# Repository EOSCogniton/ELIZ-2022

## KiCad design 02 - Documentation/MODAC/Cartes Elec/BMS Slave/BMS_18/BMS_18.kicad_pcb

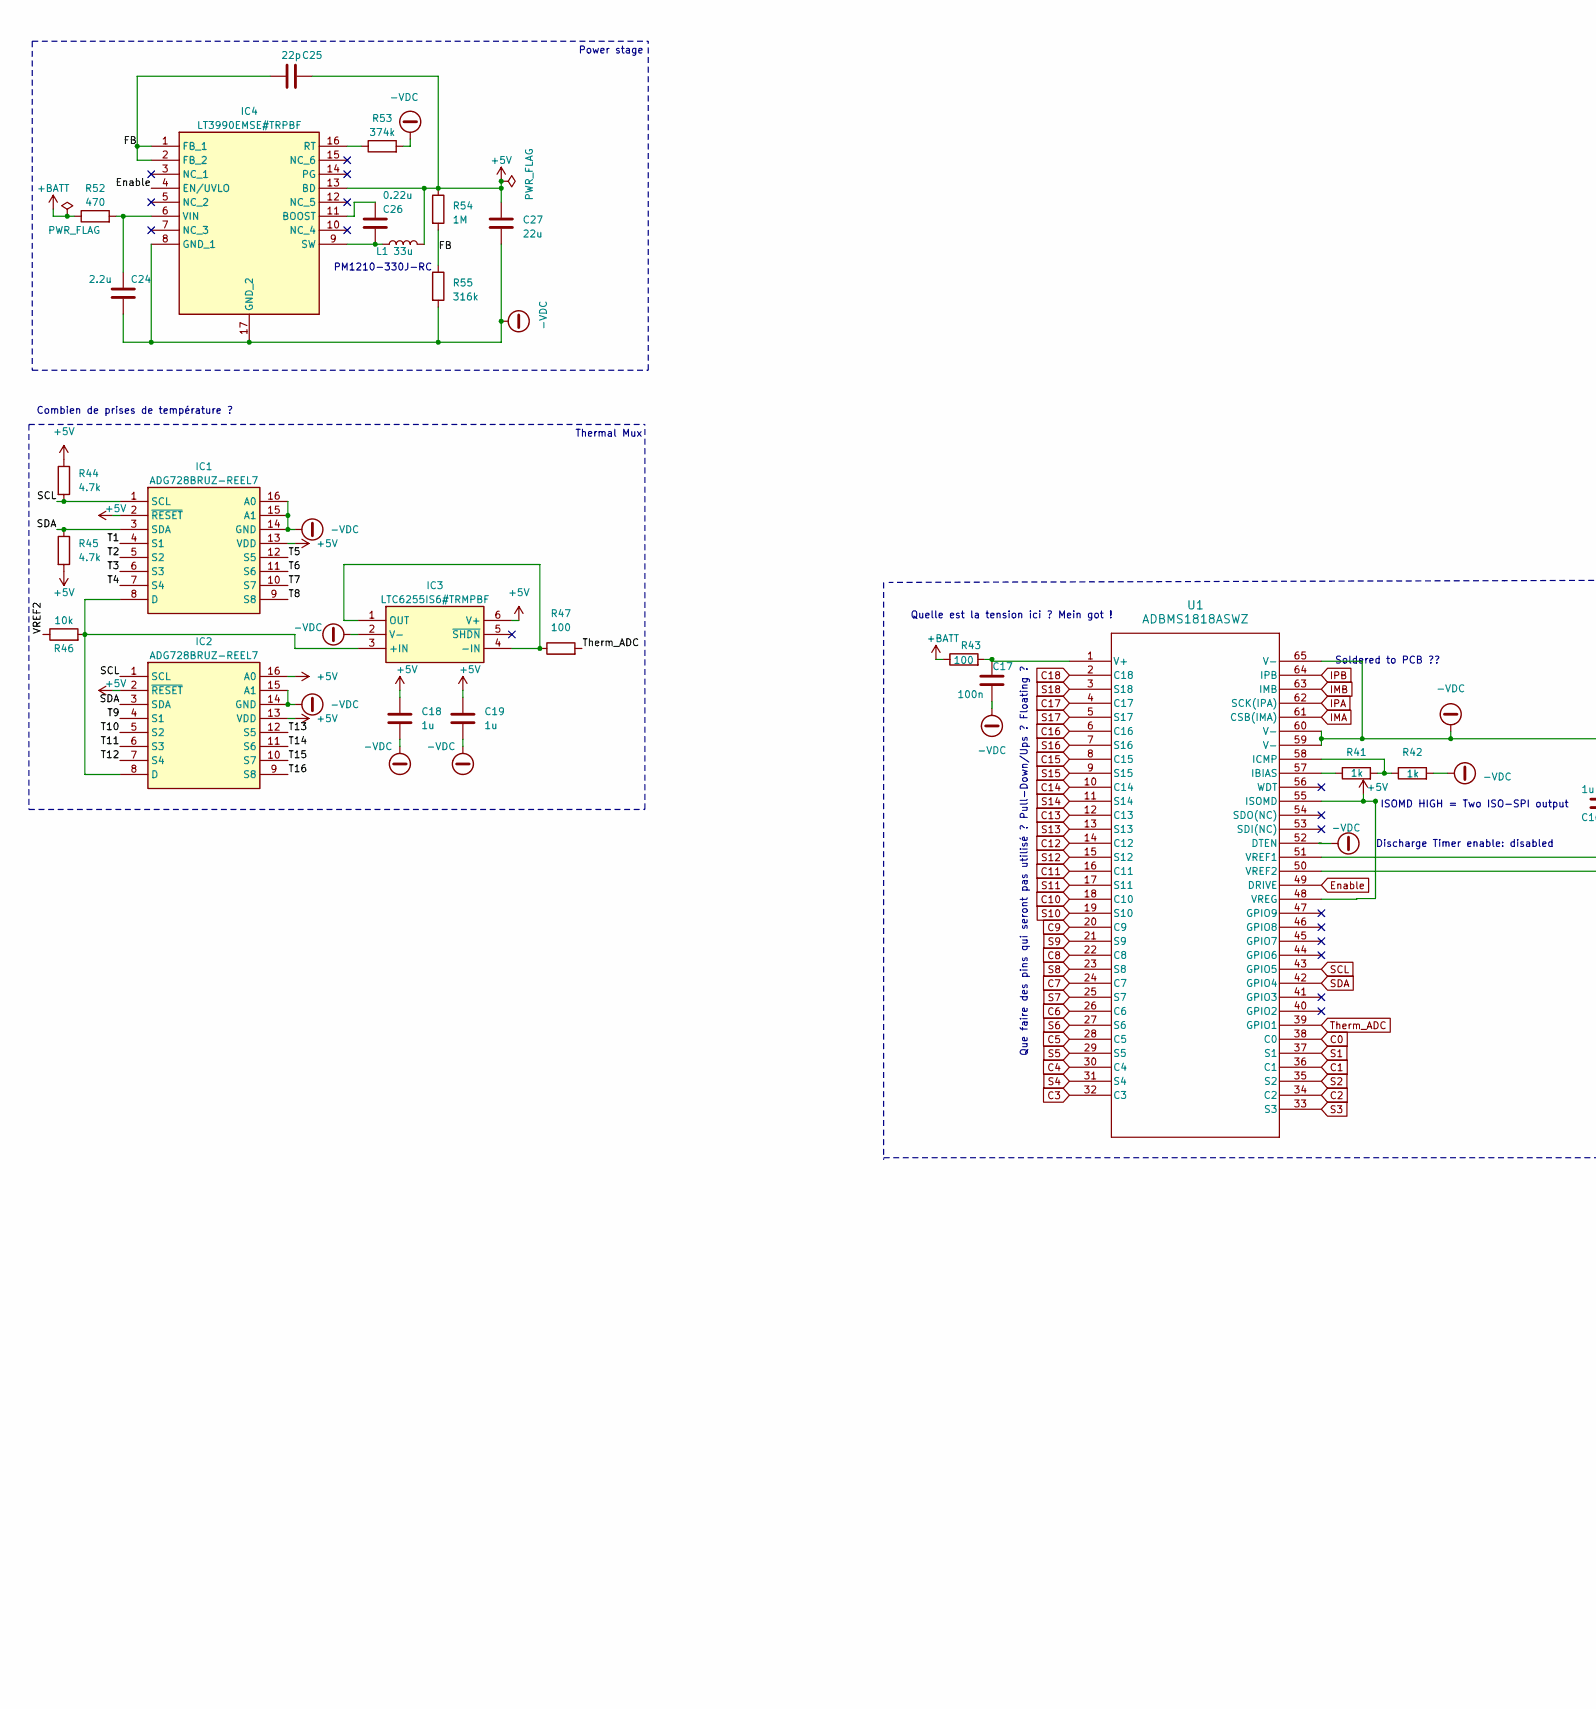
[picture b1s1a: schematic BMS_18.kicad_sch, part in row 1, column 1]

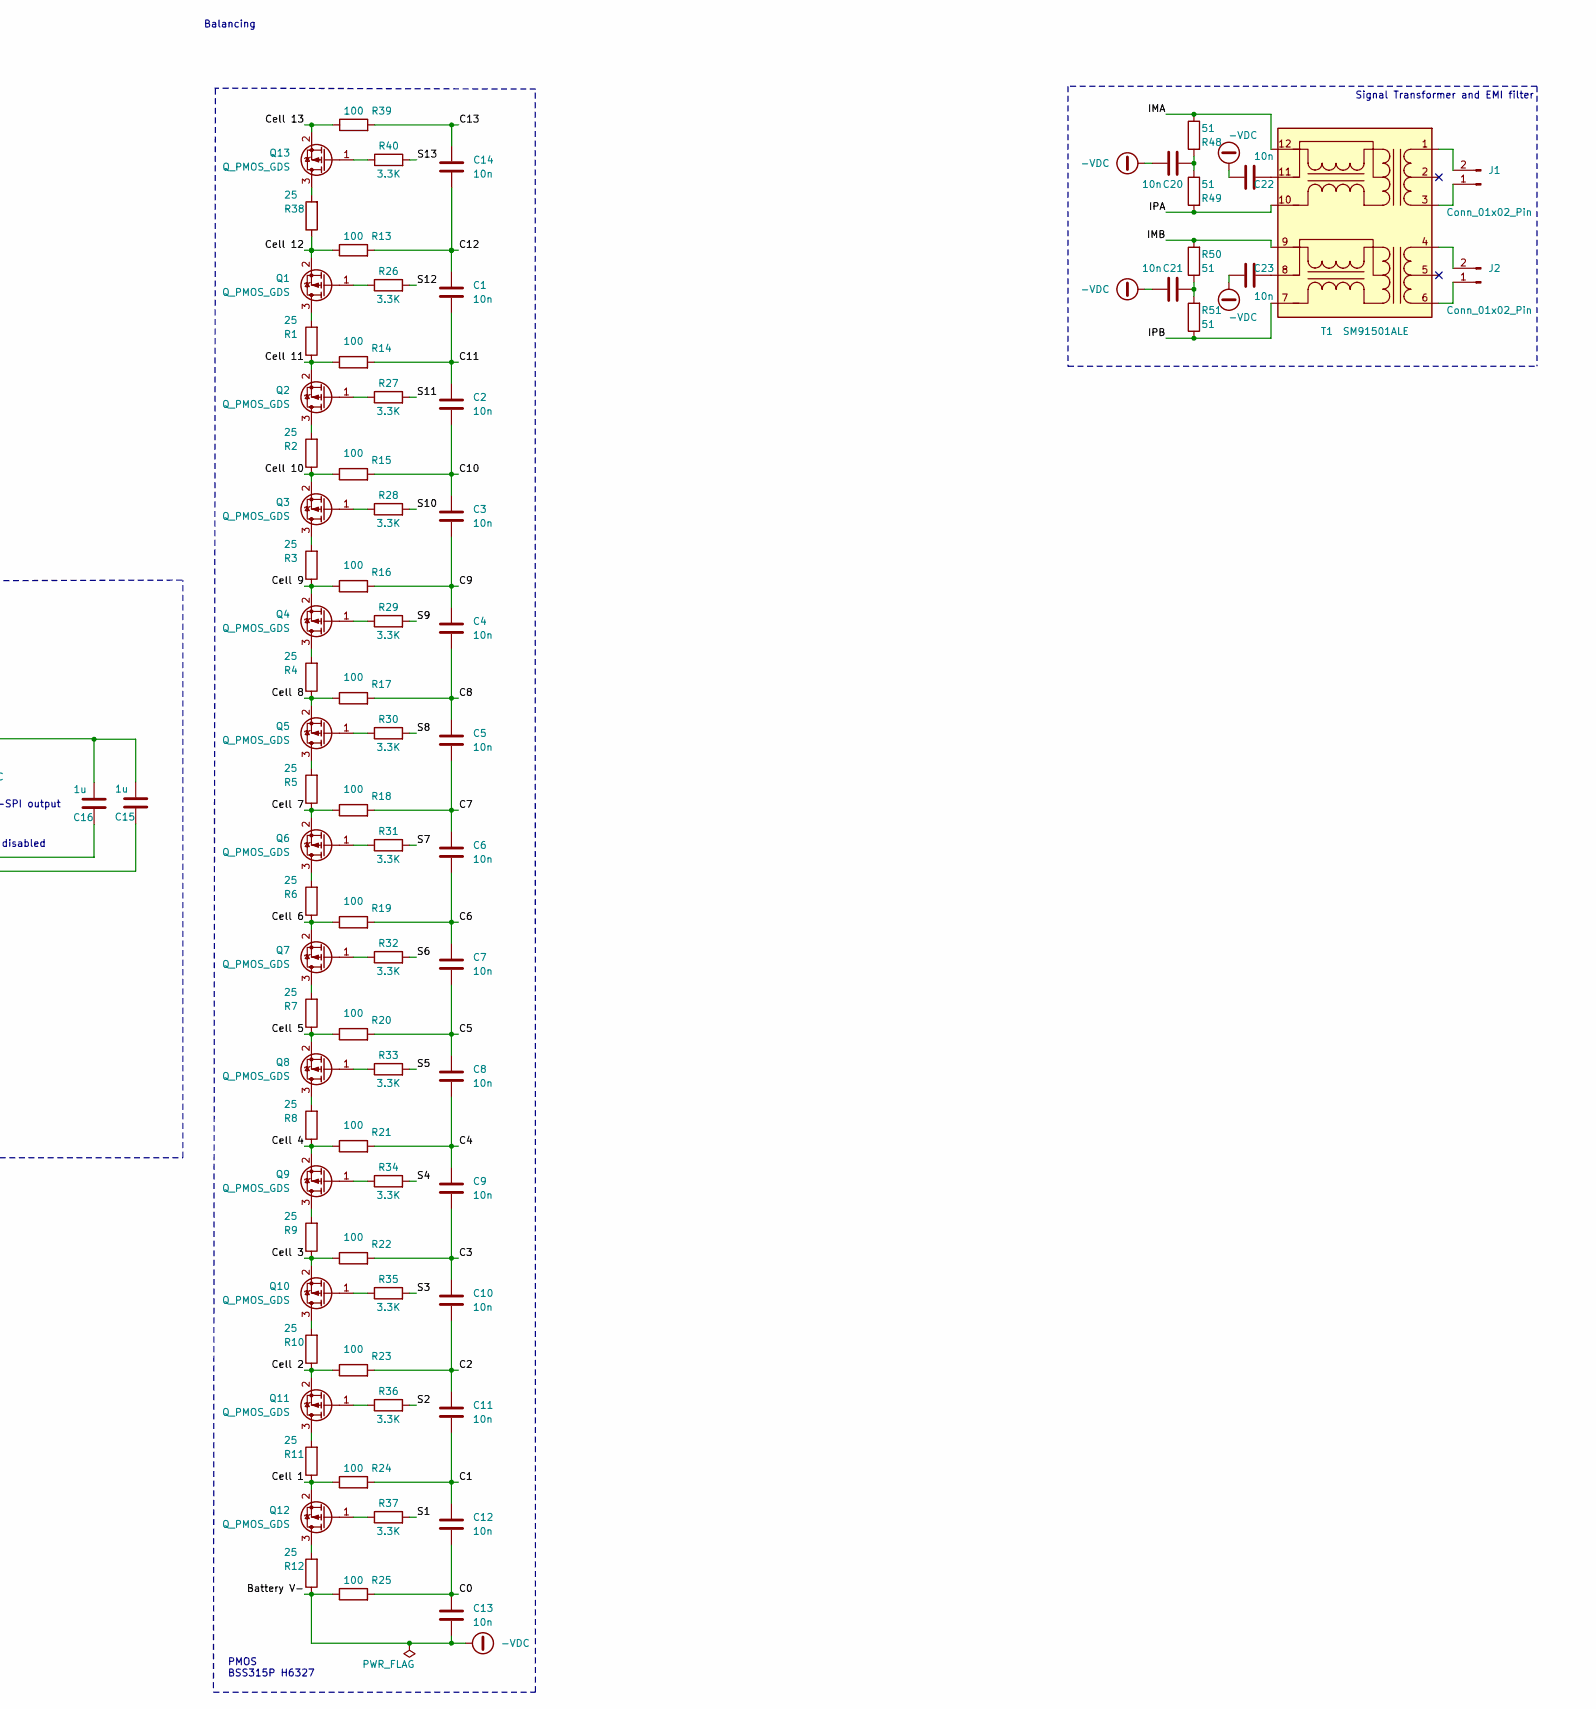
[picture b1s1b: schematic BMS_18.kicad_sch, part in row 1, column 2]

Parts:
C1, C2, C3, C4, C5, C6, C7, C8, C9, C10, C11, C12, C13, C14, C20, C21, C22, C23: 10n; C_0805_2012Metric_Pad1.18x1.45mm_HandSolder
C15, C16, C18, C19: 1u; C_0805_2012Metric_Pad1.18x1.45mm_HandSolder
C17: 100n; C_0805_2012Metric_Pad1.18x1.45mm_HandSolder
C24: 2.2u; C_0805_2012Metric_Pad1.18x1.45mm_HandSolder
C25: 22p; C_0805_2012Metric_Pad1.18x1.45mm_HandSolder
C26: 0.22u; C_0805_2012Metric_Pad1.18x1.45mm_HandSolder
C27: 22u; C_0805_2012Metric_Pad1.18x1.45mm_HandSolder
IC1, IC2: ADG728BRUZ-REEL7; SOP65P640X120-16N; Mouser Part Number 584-ADG728BRUZ-R7
IC3: LTC6255IS6#TRMPBF; SOT95P280X100-6N; Mouser Part Number 584-LTC6255IS6TRMPBF
IC4: LT3990EMSE#TRPBF; SOP50P490X110-17N; Mouser Part Number 584-LT3990EMSE#TRPBF
J1, J2: Conn_01x02_Pin; RHDR2W97P0X254_1X2_654X508X1379P
L1: 33u; L_1210_3225Metric_Pad1.42x2.65mm_HandSolder
Q1, Q2, Q3, Q4, Q5, Q6, Q7, Q8, Q9, Q10, Q11, Q12, Q13: Q_PMOS_GDS; SOT95P237X112-3N
R1, R2, R3, R4, R5, R6, R7, R8, R9, R10, R11, R12, R38: 25; R_2512_6332Metric_Pad1.40x3.35mm_HandSolder
R13, R14, R15, R16, R17, R18, R19, R20, R21, R22, R23, R24, R25, R39, R43, R47: 100; R_1206_3216Metric_Pad1.30x1.75mm_HandSolder
R26, R27, R28, R29, R30, R31, R32, R33, R34, R35, R36, R37, R40: 3.3K; R_1206_3216Metric_Pad1.30x1.75mm_HandSolder
R41, R42: 1k; R_1206_3216Metric_Pad1.30x1.75mm_HandSolder
R44, R45: 4.7k; R_1206_3216Metric_Pad1.30x1.75mm_HandSolder
R46: 10k; R_1206_3216Metric_Pad1.30x1.75mm_HandSolder
R48, R49, R50, R51: 51; R_1206_3216Metric_Pad1.30x1.75mm_HandSolder
R52: 470; R_1206_3216Metric_Pad1.30x1.75mm_HandSolder
R53: 374k; R_1206_3216Metric_Pad1.30x1.75mm_HandSolder
R54: 1M; R_1206_3216Metric_Pad1.30x1.75mm_HandSolder
R55: 316k; R_1206_3216Metric_Pad1.30x1.75mm_HandSolder
T1: SM91501ALE; SOP200P1473X500-12N; Mouser Part Number 652-SM91501ALE
U1: ADBMS1818ASWZ; 05-08-1982_ADI

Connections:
+5V: C18.1, C19.1, C25.2, C27.2, IC1.2 (~RESET), IC1.13 (VDD), IC2.2 (~RESET), IC2.13 (VDD), IC2.16 (A0), IC3.6 (V+), IC4.13 (BD), L1.2, R44.1, R45.2, R54.1, U1.48 (VREG), U1.55 (ISOMD)
+BATT: R43.1, R52.1
-VDC: C13.2, C15.2, C16.2, C17.2, C18.2, C19.2, C20.1, C21.1, C22.1, C23.1, C24.1, C27.1, IC1.14 (GND), IC1.15 (A1), IC1.16 (A0), IC2.14 (GND), IC2.15 (A1), IC3.2 (V-), IC4.8 (GND_1), IC4.17 (GND_2), R12.1, R25.1, R42.2, R53.2, R55.2, U1.52 (DTEN), U1.59 (V-), U1.60 (V-), U1.65 (V-)
/Cell 1: Q12.2 (S), R11.1, R24.1
/Cell 2: Q11.2 (S), R10.1, R23.1
/Cell 3: Q10.2 (S), R9.1, R22.1
/Cell 4: Q9.2 (S), R8.1, R21.1
/Cell 5: Q8.2 (S), R7.1, R20.1
/Cell 6: Q7.2 (S), R6.1, R19.1
/Cell 7: Q6.2 (S), R5.1, R18.1
/Cell 8: Q5.2 (S), R4.1, R17.1
/Cell 9: Q4.2 (S), R3.1, R16.1
/Cell 10: Q3.2 (S), R2.1, R15.1
/Cell 11: Q2.2 (S), R1.1, R14.1
/Cell 12: Q1.2 (S), R13.1, R38.1
/Cell 13: Q13.2 (S), R39.1
/FB: C25.1, IC4.1 (FB_1), IC4.2 (FB_2), R54.2, R55.1
/T1: IC1.4 (S1)
/T2: IC1.5 (S2)
/T3: IC1.6 (S3)
/T4: IC1.7 (S4)
/T5: IC1.12 (S5)
/T6: IC1.11 (S6)
/T7: IC1.10 (S7)
/T8: IC1.9 (S8)
/T9: IC2.4 (S1)
/T10: IC2.5 (S2)
/T11: IC2.6 (S3)
/T12: IC2.7 (S4)
/T13: IC2.12 (S5)
/T14: IC2.11 (S6)
/T15: IC2.10 (S7)
/T16: IC2.9 (S8)
/VREF2: R46.1
C0: C12.2, C13.1, R25.2, U1.38 (C0)
C1: C11.2, C12.1, R24.2, U1.36 (C1)
C2: C10.2, C11.1, R23.2, U1.34 (C2)
C3: C9.2, C10.1, R22.2, U1.32 (C3)
C4: C8.2, C9.1, R21.2, U1.30 (C4)
C5: C7.2, C8.1, R20.2, U1.28 (C5)
C6: C6.2, C7.1, R19.2, U1.26 (C6)
C7: C5.2, C6.1, R18.2, U1.24 (C7)
C8: C4.2, C5.1, R17.2, U1.22 (C8)
C9: C3.2, C4.1, R16.2, U1.20 (C9)
C10: C2.2, C3.1, R15.2, U1.18 (C10)
C11: C1.2, C2.1, R14.2, U1.16 (C11)
C12: C1.1, C14.2, R13.2, U1.14 (C12)
C13: C14.1, R39.2, U1.12 (C13)
C14: U1.10 (C14)
C15: U1.8 (C15)
C16: U1.6 (C16)
C17: U1.4 (C17)
C18: U1.2 (C18)
Enable: IC4.4 (EN/UVLO), U1.49 (DRIVE)
IMA: R48.1, T1.12 (SEC1_3), U1.61 (CSB(IMA))
IMB: R50.2, T1.9 (SEC2_3), U1.63 (IMB)
IPA: R49.2, T1.10 (SEC1_1), U1.62 (SCK(IPA))
IPB: R51.1, T1.7 (SEC2_1), U1.64 (IPB)
unnamed: C20.2, R48.2, R49.1
unnamed: C21.2, R50.1, R51.2
unnamed: IC1.8 (D), IC2.8 (D), IC3.3 (+IN), R46.2
unnamed: IC3.1 (OUT), IC3.4 (-IN), R47.1
unnamed: C26.2, IC4.11 (BOOST)
unnamed: IC4.16 (RT), R53.1
unnamed: C26.1, IC4.9 (SW), L1.1
unnamed: C24.2, IC4.6 (VIN), R52.2
unnamed: J1.1, T1.3 (PRI1_3)
unnamed: J1.2, T1.1 (PRI1_1)
unnamed: J2.1, T1.6 (PRI2_3)
unnamed: J2.2, T1.4 (PRI2_1)
unnamed: Q1.3 (D), R1.2
unnamed: Q1.1 (G), R26.1
unnamed: Q2.3 (D), R2.2
unnamed: Q2.1 (G), R27.1
unnamed: Q3.3 (D), R3.2
unnamed: Q3.1 (G), R28.1
unnamed: Q4.3 (D), R4.2
unnamed: Q4.1 (G), R29.1
unnamed: Q5.3 (D), R5.2
unnamed: Q5.1 (G), R30.1
unnamed: Q6.3 (D), R6.2
unnamed: Q6.1 (G), R31.1
unnamed: Q7.3 (D), R7.2
unnamed: Q7.1 (G), R32.1
unnamed: Q8.3 (D), R8.2
unnamed: Q8.1 (G), R33.1
unnamed: Q9.3 (D), R9.2
unnamed: Q9.1 (G), R34.1
unnamed: Q10.3 (D), R10.2
unnamed: Q10.1 (G), R35.1
unnamed: Q11.3 (D), R11.2
unnamed: Q11.1 (G), R36.1
unnamed: Q12.3 (D), R12.2
unnamed: Q12.1 (G), R37.1
unnamed: Q13.3 (D), R38.2
unnamed: Q13.1 (G), R40.1
unnamed: C22.2, T1.11 (SEC1_2)
unnamed: C23.2, T1.8 (SEC2_2)
unnamed: R41.1, U1.57 (IBIAS)
unnamed: R41.2, R42.1, U1.58 (ICMP)
unnamed: C17.1, R43.2, U1.1 (V+)
unnamed: C16.1, U1.51 (VREF1)
unnamed: C15.1, U1.50 (VREF2)
S1: R37.2, U1.37 (S1)
S2: R36.2, U1.35 (S2)
S3: R35.2, U1.33 (S3)
S4: R34.2, U1.31 (S4)
S5: R33.2, U1.29 (S5)
S6: R32.2, U1.27 (S6)
S7: R31.2, U1.25 (S7)
S8: R30.2, U1.23 (S8)
S9: R29.2, U1.21 (S9)
S10: R28.2, U1.19 (S10)
S11: R27.2, U1.17 (S11)
S12: R26.2, U1.15 (S12)
S13: R40.2, U1.13 (S13)
S14: U1.11 (S14)
S15: U1.9 (S15)
S16: U1.7 (S16)
S17: U1.5 (S17)
S18: U1.3 (S18)
SCL: IC1.1 (SCL), IC2.1 (SCL), R44.2, U1.43 (GPIO5)
SDA: IC1.3 (SDA), IC2.3 (SDA), R45.1, U1.42 (GPIO4)
Therm_ADC: R47.2, U1.39 (GPIO1)

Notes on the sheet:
PM1210-330J-RC
Combien de prises de température ?
Signal Transformer and EMI filter
Discharge Timer enable: disabled
Quelle est la tension ici ? Mein got !
Soldered to PCB ??
Power stage
Balancing
Thermal Mux
ISOMD HIGH = Two ISO-SPI output
Que faire des pins qui seront pas utilisé ? Pull-Down/Ups ? Floating ?
PMOS BSS315P H6327

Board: 2 copper layers, 104 parts (0 on the bottom side), 97 nets, no tracks yet.

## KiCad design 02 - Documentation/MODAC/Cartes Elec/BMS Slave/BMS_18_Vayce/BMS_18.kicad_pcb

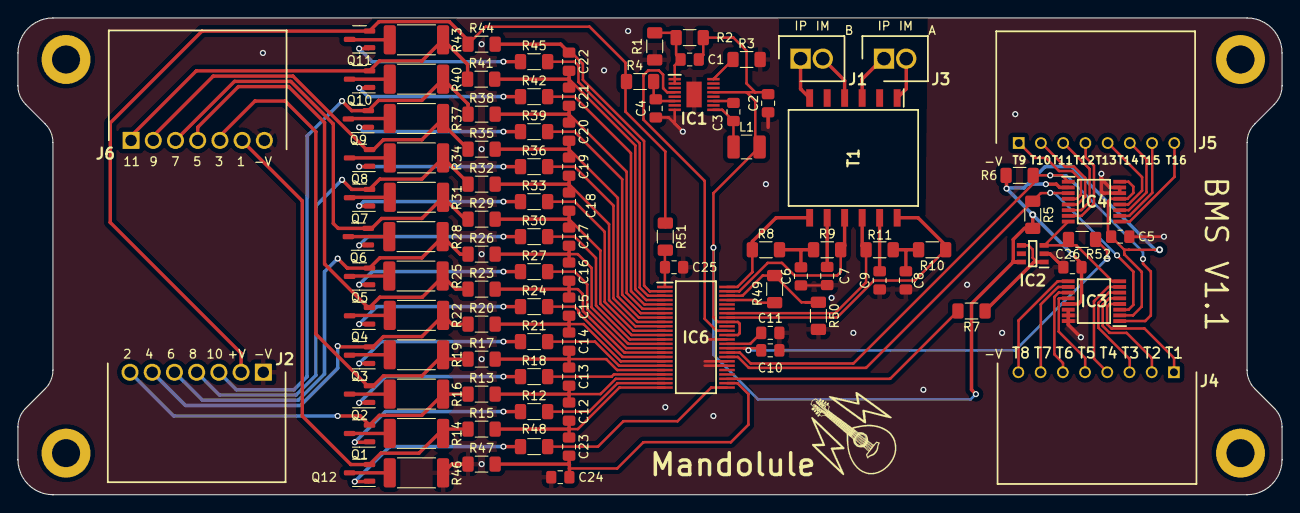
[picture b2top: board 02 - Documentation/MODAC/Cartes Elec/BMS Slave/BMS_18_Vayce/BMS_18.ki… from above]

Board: 2 copper layers, 144.5 x 54.5 mm, 104 parts (0 on the bottom side), 107 nets.

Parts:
C1: 22p; C_0805_2012Metric_Pad1.18x1.45mm_HandSolder
C2: 22u; C_0805_2012Metric_Pad1.18x1.45mm_HandSolder
C3: 0.22u; C_0805_2012Metric_Pad1.18x1.45mm_HandSolder
C4: 2.2u; C_0805_2012Metric_Pad1.18x1.45mm_HandSolder
C5, C10, C11, C26: 1u; C_0805_2012Metric_Pad1.18x1.45mm_HandSolder
C6, C7, C8, C9, C12, C13, C14, C15, C16, C17, C18, C19, C20, C21, C22, C23, C24: 10n; C_0805_2012Metric_Pad1.18x1.45mm_HandSolder
C25: 100n; C_0805_2012Metric_Pad1.18x1.45mm_HandSolder
IC1: LT3990EMSE#TRPBF; SOP50P490X110-17N
IC2: LTC6255IS6#TRMPBF; SOT95P280X100-6N
IC3, IC4: ADG728BRUZ-REEL7; SOP65P640X120-16N
IC6: LTC6811IG-1#PBF; SOP50P780X200-48N
J1, J3: Conn_01x02_Pin; RHDR2W97P0X254_1X2_654X508X1379P
J2, J6: Conn_01x07_Pin; SHDRRA7W77P0X254_1X7_2032X1359X699P
J4, J5: Conn_01x08_Pin; SHDRRA8W50P0X254_1X8_2273X1359X741P
L1: 33u; L_1210_3225Metric_Pad1.42x2.65mm_HandSolder
Q1, Q2, Q3, Q4, Q5, Q6, Q7, Q8, Q9, Q10, Q11, Q12: Q_PMOS_GDS; SOT-23-3
R1: 316k; R_1206_3216Metric_Pad1.30x1.75mm_HandSolder
R2: 1M; R_1206_3216Metric_Pad1.30x1.75mm_HandSolder
R3: 374k; R_1206_3216Metric_Pad1.30x1.75mm_HandSolder
R4: 470; R_1206_3216Metric_Pad1.30x1.75mm_HandSolder
R5, R6: 4.7k; R_1206_3216Metric_Pad1.30x1.75mm_HandSolder
R7, R13, R15, R17, R20, R23, R26, R29, R32, R35, R38, R41, R44, R47, R51: 100; R_1206_3216Metric_Pad1.30x1.75mm_HandSolder
R8, R9, R10, R11: 51; R_1206_3216Metric_Pad1.30x1.75mm_HandSolder
R12, R18, R21, R24, R27, R30, R33, R36, R39, R42, R45, R48: 3.3K; R_1206_3216Metric_Pad1.30x1.75mm_HandSolder
R14, R16, R19, R22, R25, R28, R31, R34, R37, R40, R43, R46: 25; R_2512_6332Metric_Pad1.40x3.35mm_HandSolder
R49, R50: 1k; R_1206_3216Metric_Pad1.30x1.75mm_HandSolder
R52: 10k; R_1206_3216Metric_Pad1.30x1.75mm_HandSolder
Ref**: Val**; Mandolule Silk
T1: SM91501ALE; SOP200P1473X500-12N

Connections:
+5V: C1.2, C2.2, C5.1, C26.1, IC1.13 (BD), IC2.6 (V+), IC3.2 (~RESET), IC3.13 (VDD), IC4.2 (~RESET), IC4.13 (VDD), IC4.16 (A0), IC6.37 (VREG), IC6.40 (ISOMD), L1.2, R2.1, R5.2, R6.1
+BATT: J2.2, Q11.2 (S), R4.1, R44.1, R51.1
-VDC: C2.1, C4.1, C5.2, C6.1, C7.1, C8.1, C9.1, C10.2, C11.2, C24.2, C25.2, C26.2, IC1.8 (GND_1), IC1.17 (GND_2), IC2.2 (V-), IC3.14 (GND), IC3.15 (A1), IC3.16 (A0), IC4.14 (GND), IC4.15 (A1), IC6.30 (V-_1), IC6.31 (V-_2), IC6.36 (DTEN), J2.1, J6.7, R1.2, R3.2, R46.1, R47.1, R50.2
/C0: C23.2, C24.1, IC6.26 (C0), R47.2
/C1: C12.2, C23.1, IC6.24 (C1), R15.2
/C2: C12.1, C13.2, IC6.22 (C2), R13.2
/C3: C13.1, C14.2, IC6.20 (C3), R17.2
/C4: C14.1, C15.2, IC6.18 (C4), R20.2
/C5: C15.1, C16.2, IC6.16 (C5), R23.2
/C6: C16.1, C17.2, IC6.14 (C6), R26.2
/C7: C17.1, C18.2, IC6.12 (C7), R29.2
/C8: C18.1, C19.2, IC6.10 (C8), R32.2
/C9: C19.1, C20.2, IC6.8 (C9), R35.2
/C10: C20.1, C21.2, IC6.6 (C10), R38.2
/C11: C21.1, C22.2, IC6.4 (C11), R41.2
/C12: C22.1, IC6.2 (C12), R44.2
/Cell 1: J6.6, Q12.2 (S), R14.1, R15.1
/Cell 2: J2.7, Q1.2 (S), R13.1, R16.1
/Cell 3: J6.5, Q2.2 (S), R17.1, R19.1
/Cell 4: J2.6, Q3.2 (S), R20.1, R22.1
/Cell 5: J6.4, Q4.2 (S), R23.1, R25.1
/Cell 6: J2.5, Q5.2 (S), R26.1, R28.1
/Cell 7: J6.3, Q6.2 (S), R29.1, R31.1
/Cell 8: J2.4, Q7.2 (S), R32.1, R34.1
/Cell 9: J6.2, Q8.2 (S), R35.1, R37.1
/Cell 10: J2.3, Q9.2 (S), R38.1, R40.1
/Cell 11: J6.1, Q10.2 (S), R41.1, R43.1
/Enable: IC1.4 (EN/UVLO), IC6.38 (DRIVE)
/FB: C1.1, IC1.1 (FB_1), IC1.2 (FB_2), R1.1, R2.2
/IMA: IC6.41 (CSB_(IMA)), R10.1, T1.12 (SEC1_3)
/IMB: IC6.47 (IMB), R9.2, T1.9 (SEC2_3)
/IPA: IC6.42 (SCK_(IPA)), R11.2, T1.10 (SEC1_1)
/IPB: IC6.48 (IPB), R8.1, T1.7 (SEC2_1)
/S1: IC6.25 (S1), R48.2
/S2: IC6.23 (S2), R12.2
/S3: IC6.21 (S3), R18.2
/S4: IC6.19 (S4), R21.2
/S5: IC6.17 (S5), R24.2
/S6: IC6.15 (S6), R27.2
/S7: IC6.13 (S7), R30.2
/S8: IC6.11 (S8), R33.2
/S9: IC6.9 (S9), R36.2
/S10: IC6.7 (S10), R39.2
/S11: IC6.5 (S11), R42.2
/S12: IC6.3 (S12), R45.2
/SCL: IC3.1 (SCL), IC4.1 (SCL), IC6.33 (GPIO5), R6.2
/SDA: IC3.3 (SDA), IC4.3 (SDA), IC6.32 (GPIO4), R5.1
/T1: IC3.4 (S1), J4.1
/T2: IC3.5 (S2), J4.2
/T3: IC3.6 (S3), J4.3
/T4: IC3.7 (S4), J4.4
/T5: IC3.12 (S5), J4.5
/T6: IC3.11 (S6), J4.6
/T7: IC3.10 (S7), J4.7
/T8: IC3.9 (S8), J4.8
/T9: IC4.4 (S1), J5.1
/T10: IC4.5 (S2), J5.2
/T11: IC4.6 (S3), J5.3
/T12: IC4.7 (S4), J5.4
/T13: IC4.12 (S5), J5.5
/T14: IC4.11 (S6), J5.6
/T15: IC4.10 (S7), J5.7
/T16: IC4.9 (S8), J5.8
/Therm_ADC: IC6.27 (GPIO1), R7.2
/VREF2: C10.1, IC6.34 (VREF2), R52.1
unnamed: C6.2, R8.2, R9.1
unnamed: C8.2, R10.2, R11.1
unnamed: C3.2, IC1.11 (BOOST)
unnamed: IC1.16 (RT), R3.1
unnamed: C3.1, IC1.9 (SW), L1.1
unnamed: C4.2, IC1.6 (VIN), R4.2
unnamed: IC2.3 (+IN), IC3.8 (D), IC4.8 (D), R52.2
unnamed: IC2.1 (OUT), IC2.4 (-IN), R7.1
unnamed: IC6.45 (IBIAS), R49.1
unnamed: IC6.46 (ICMP), R49.2, R50.1
unnamed: C25.1, IC6.1 (V+), R51.2
unnamed: C11.1, IC6.35 (VREF1)
unnamed: J1.1, T1.6 (PRI2_3)
unnamed: J1.2, T1.4 (PRI2_1)
unnamed: J3.1, T1.3 (PRI1_3)
unnamed: J3.2, T1.1 (PRI1_1)
unnamed: Q1.3 (D), R14.2
unnamed: Q1.1 (G), R12.1
unnamed: Q2.3 (D), R16.2
unnamed: Q2.1 (G), R18.1
unnamed: Q3.3 (D), R19.2
unnamed: Q3.1 (G), R21.1
unnamed: Q4.3 (D), R22.2
unnamed: Q4.1 (G), R24.1
unnamed: Q5.3 (D), R25.2
unnamed: Q5.1 (G), R27.1
unnamed: Q6.3 (D), R28.2
unnamed: Q6.1 (G), R30.1
unnamed: Q7.3 (D), R31.2
unnamed: Q7.1 (G), R33.1
unnamed: Q8.3 (D), R34.2
unnamed: Q8.1 (G), R36.1
unnamed: Q9.3 (D), R37.2
unnamed: Q9.1 (G), R39.1
unnamed: Q10.3 (D), R40.2
unnamed: Q10.1 (G), R42.1
unnamed: Q11.3 (D), R43.2
unnamed: Q11.1 (G), R45.1
unnamed: Q12.3 (D), R46.2
unnamed: Q12.1 (G), R48.1
unnamed: C9.2, T1.11 (SEC1_2)
unnamed: C7.2, T1.8 (SEC2_2)

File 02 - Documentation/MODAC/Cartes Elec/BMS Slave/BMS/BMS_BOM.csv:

"Designator","Comment","Footprint"
"C1","22p","Capacitor_SMD:C_0805_2012Metric_Pad1.18x1.45mm_HandSolder"
"C2","22u","Capacitor_SMD:C_0805_2012Metric_Pad1.18x1.45mm_HandSolder"
"C3","0.22u","Capacitor_SMD:C_0805_2012Metric_Pad1.18x1.45mm_HandSolder"
"C4","2.2u","Capacitor_SMD:C_0805_2012Metric_Pad1.18x1.45mm_HandSolder"
"C5,C10,C11,C26","1u","Capacitor_SMD:C_0805_2012Metric_Pad1.18x1.45mm_HandSolder"
"C6,C7,C8,C9,C12,C13,C14,C15,C16,C17,C18,C19,C20,C21,C22,C23,C24","10n","Capacitor_SMD:C_0805_2012Metric_Pad1.18x1.45mm_HandSolder"
"C25","100n","Capacitor_SMD:C_0805_2012Metric_Pad1.18x1.45mm_HandSolder"
"IC1","LT3990EMSE#TRPBF","EPSA:SOP50P490X110-17N"
"IC2","LTC6255IS6#TRMPBF","EPSA:SOT95P280X100-6N"
"IC3,IC4","ADG728BRUZ-REEL7","EPSA:SOP65P640X120-16N"
"IC6","LTC6811IG-1#PBF","EPSA:SOP50P780X200-48N"
"J1,J3","Conn_01x02_Pin","EPSA:RHDR2W97P0X254_1X2_654X508X1379P"
"J2,J6","Conn_01x07_Pin","EPSA:SHDRRA7W77P0X254_1X7_2032X1359X699P"
"J4,J5","Conn_01x08_Pin","EPSA:SHDRRA9W69P0X254_1X9_2527X1359X741P"
"L1","33u","Inductor_SMD:L_1210_3225Metric_Pad1.42x2.65mm_HandSolder"
"Q1,Q2,Q3,Q4,Q5,Q6,Q7,Q8,Q9,Q10,Q11,Q12","Q_PMOS_GDS","EPSA:SOT-23-3"
"R1","316k","Resistor_SMD:R_1206_3216Metric_Pad1.30x1.75mm_HandSolder"
"R2","1M","Resistor_SMD:R_1206_3216Metric_Pad1.30x1.75mm_HandSolder"
"R3","374k","Resistor_SMD:R_1206_3216Metric_Pad1.30x1.75mm_HandSolder"
"R4","470","Resistor_SMD:R_1206_3216Metric_Pad1.30x1.75mm_HandSolder"
"R5,R6","4.7k","Resistor_SMD:R_1206_3216Metric_Pad1.30x1.75mm_HandSolder"
"R7,R13,R15,R17,R20,R23,R26,R29,R32,R35,R38,R41,R44,R47,R51","100","Resistor_SMD:R_1206_3216Metric_Pad1.30x1.75mm_HandSolder"
"R8,R9,R10,R11","51","Resistor_SMD:R_1206_3216Metric_Pad1.30x1.75mm_HandSolder"
"R12,R18,R21,R24,R27,R30,R33,R36,R39,R42,R45,R48","3.3K","Resistor_SMD:R_1206_3216Metric_Pad1.30x1.75mm_HandSolder"
"R14,R16,R19,R22,R25,R28,R31,R34,R37,R40,R43,R46","25","Resistor_SMD:R_2512_6332Metric_Pad1.40x3.35mm_HandSolder"
"R49,R50","1k","Resistor_SMD:R_1206_3216Metric_Pad1.30x1.75mm_HandSolder"
"R52","10k","Resistor_SMD:R_1206_3216Metric_Pad1.30x1.75mm_HandSolder"
"T1","SM91501ALE","EPSA:SOP200P1473X500-12N"

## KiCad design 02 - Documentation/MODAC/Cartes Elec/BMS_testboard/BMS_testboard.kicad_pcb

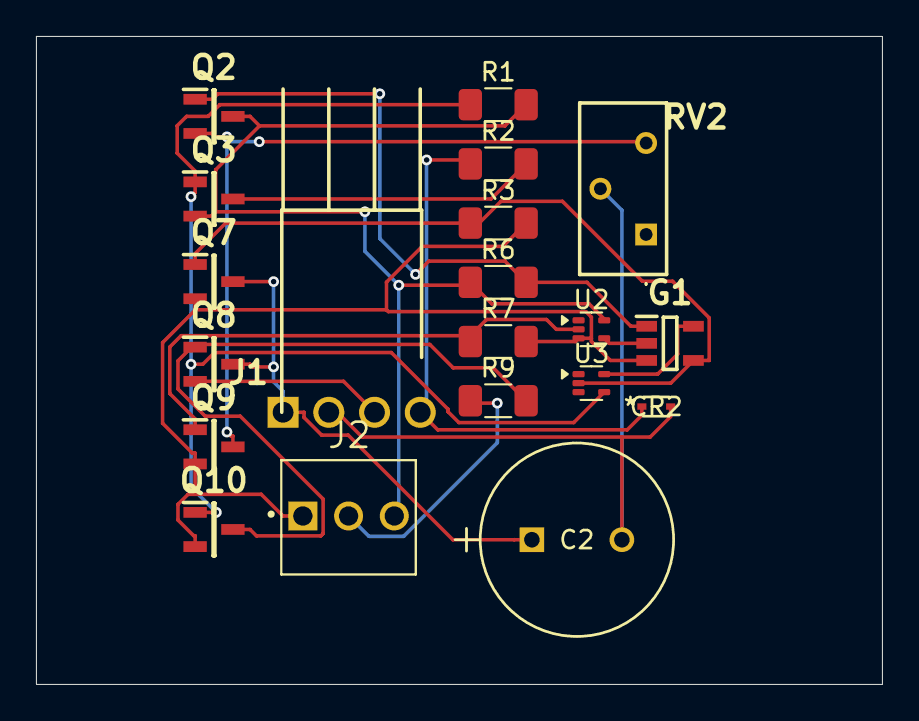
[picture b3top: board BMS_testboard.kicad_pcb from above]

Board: 2 copper layers, 47.0 x 36.0 mm, 20 parts (0 on the bottom side), 15 nets.

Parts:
C2: MAL204835102E3; CAP_038RSU_10X20X.6_VIS
CR2: RB751S40T1G; DIODE_SOD523_1P3XP9_ONS
G1: Gate NAND SN74AHCT1G00DBVR; SOT95P280X145-5N
J1: 4P Angle 171857-4004; HDRRA4W66P0X254_1X4_762X818X635P
J2: 3P Droit 22-11-2032; MOLEX_22-11-2032
Q2, Q3: PMOS SI2343CDS-T1-GE3; SOT95P237X112-3N
Q7, Q8, Q9, Q10: NMOS SQ2348ES-T1_GE3; SOT95P237X112-3N
R1, R3, R6, R7, R9: 10k; R_1206_3216Metric_Pad1.30x1.75mm_HandSolder
R2: 1k; R_1206_3216Metric_Pad1.30x1.75mm_HandSolder
RV2: Varystor 3296Y-1-223LF; 3296Y1223LF
U2, U3: 74LVC1GU04DRL; SOT-553

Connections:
+5V: G1.5 (VCC), J2.3, Q2.3, Q3.2, R1.2, R6.1, U2.5 (VCC), U3.5 (VCC)
+12V: J2.2, R9.1
A0: G1.1, Q2.1, R6.2
A1: Q9.1, R7.1, U2.2
A2: Q3.1, Q10.1, R1.1, U3.4
A3: G1.4, Q7.1, R3.1, U3.2
C_Down: CR2.1, J1.4, R2.1
C_Up: J1.3, Q8.2
GND: G1.3 (GND), J2.1, Q7.2, Q9.2, Q10.2, R3.2, R7.2, U2.3 (GND)
unnamed: G1.2, U2.4
unnamed: Q3.3, R2.2
unnamed: Q2.2, Q9.3, RV2.3 (CW)
V_cap+: C2.2, CR2.2, J1.2, RV2.2 (WIPER)
V_cap-: C2.1, J1.1, Q7.3, Q8.3
Vgate_enable: Q8.1, Q10.3, R9.2

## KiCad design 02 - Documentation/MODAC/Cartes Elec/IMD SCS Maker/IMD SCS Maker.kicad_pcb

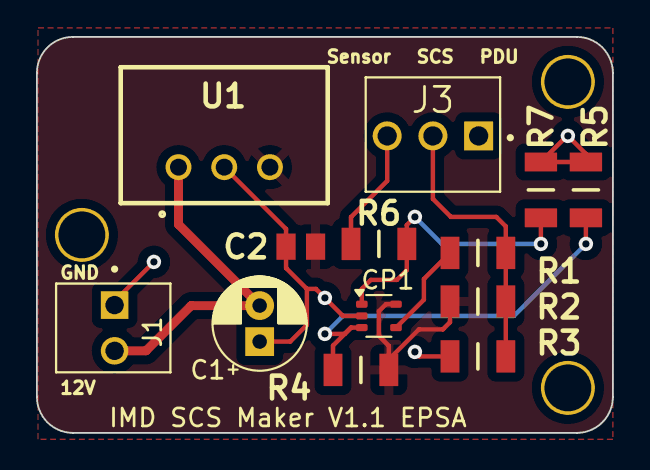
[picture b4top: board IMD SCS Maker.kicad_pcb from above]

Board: 2 copper layers, 32.0 x 22.0 mm, 13 parts (0 on the bottom side), 8 nets.

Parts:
C1: C; CP_Radial_D5.0mm_P2.00mm
C2: 10n; CAPC2012X130N
CP1: Comparator; SOT-353_SC-70-5
J1: 2P Droit 2-11-2022; MOLEX_22-11-2022
J3: 3P Droit 22-11-2032; MOLEX_22-11-2032
R1: 3k9; RESC3216X70N
R2, R3: 8k2; RESC3216X70N
R4, R5, R7: 1k; RESC3216X70N
R6: 2k; RESC3216X70N
U1: Alim LP TSR_0.5-2450; TSR-0.5-2433

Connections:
+5V: C2.2, CP1.5 (V+), R2.2, R4.2, U1.3 (+VOUT)
+12V: C1.2, J1.2, U1.1 (+VIN)
/Output SCS: J3.2, R1.1, R2.1, R3.2
/Sensor Output: J3.3, R6.2
GND: C1.1, C2.1, CP1.2 (V-), J1.1, R3.1, R5.2, R7.1, U1.2 (GND)
unnamed: CP1.1 (+), R6.1, R7.2
unnamed: CP1.3 (-), R4.1, R5.1
unnamed: CP1.4, R1.2

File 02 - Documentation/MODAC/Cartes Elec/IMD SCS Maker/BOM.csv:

"Reference","Value","Qty","Manufacturer_Name","Manufacturer_Part_Number","Mouser Part Number","Mouser Price/Stock"
"C1","C","1","","","",""
"C2","10n","1","Syfer","0805Y1000104JXT","",""
"J1","2P Droit 2-11-2022","1","","","",""
"J3","3P Droit 22-11-2032","1","Molex","22-11-2032","538-22-11-2032","https://www.mouser.fr/ProductDetail/Molex/22-11-2032?qs=KHty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"
"Q1","NMOS SQ2348ES-T1_GE3","1","Vishay","SQ2348ES-T1_GE3","781-SQ2348ES-T1_GE3","https://www.mouser.co.uk/ProductDetail/Vishay-Siliconix/SQ23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"
"R1","3k9","1","KOA Speer","RK73H2BLTDD2152F","N/A","https://www.mouser.co.uk/ProductDetail/KOA-Speer/RK73H2BLTDD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"
"R2,R3","8k2","2","KOA Speer","RK73H2BLTDD2152F","N/A","https://www.mouser.co.uk/ProductDetail/KOA-Speer/RK73H2BLTDD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"
"U1","Alim LP TSR_0.5-2450","1","Traco Power","TSR 0.5-2450","495-TSR0.5-2450","https://www.mouser.co.uk/ProductDetail/TRACO-Power/TSR-0.5-2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"

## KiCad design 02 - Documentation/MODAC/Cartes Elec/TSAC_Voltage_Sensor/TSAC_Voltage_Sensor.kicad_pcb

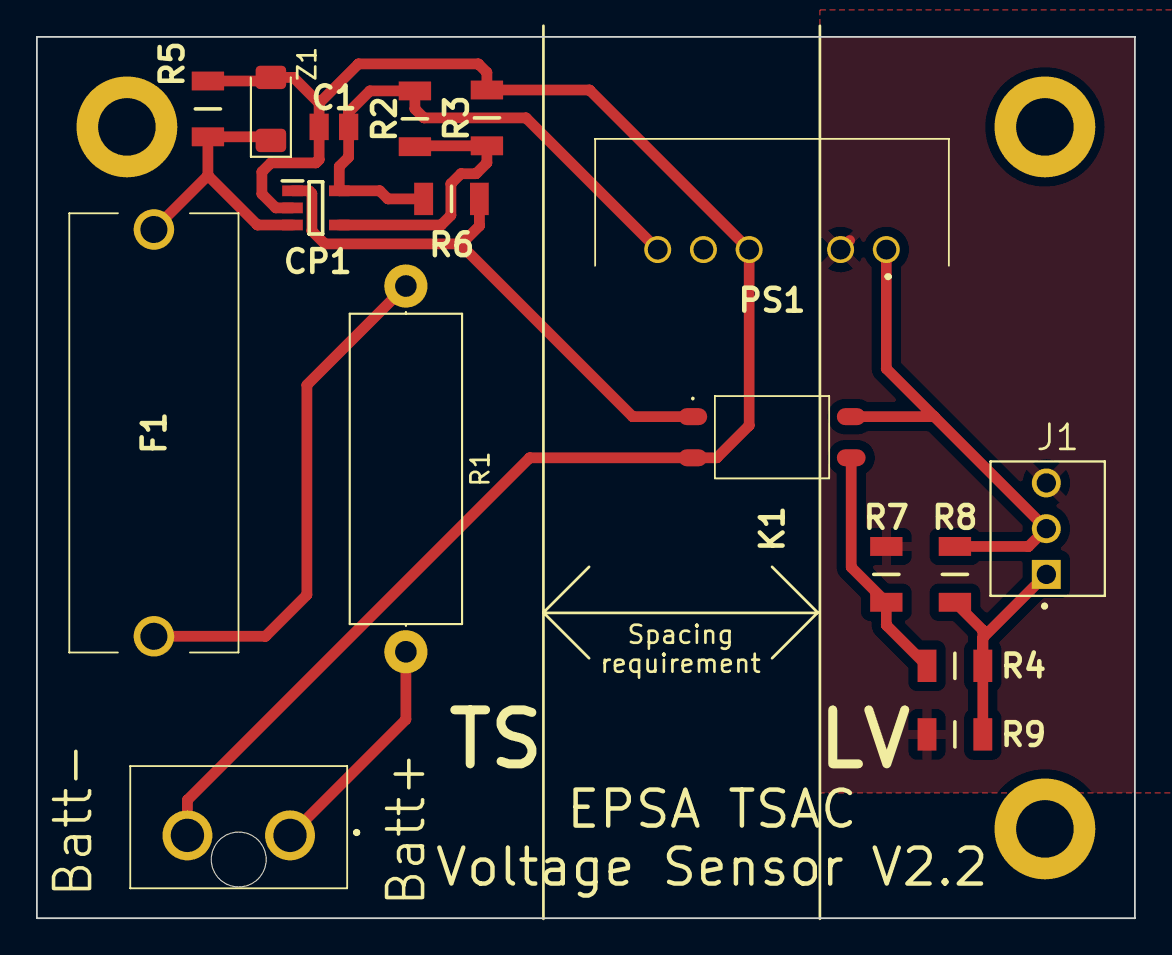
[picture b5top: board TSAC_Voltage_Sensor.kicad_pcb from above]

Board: 2 copper layers, 61.0 x 49.0 mm, 17 parts (0 on the bottom side), 11 nets.

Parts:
C1: Condensateur 0805Y1000104JXT; CAPC2012X130N
CP1: Comparateur TS391ILT; SOT95P280X145-5N
F1: Fuse; 0PTF0078P
J1: 3P Droit 22-11-2032; MOLEX_22-11-2032
J2: 200241-1112; 2002411112
K1: SSR CPC1394GR; CPC1394GR
PS1: Alim Iso PDM2-S5-S5-S; PDM2S5S5S
R1: 820k; R_Axial_DIN0617_L17.0mm_D6.0mm_P20.32mm_Horizontal
R2: 1k2; RESC3216X70N
R3: 1k; RESC3216X70N
R4: 3k9; RESC3216X70N
R5: 33k; RESC3216X70N
R6: 2k7; RESC3216X70N
R7: 2k; RESC3216X70N
R8, R9: 8k2; RESC3216X70N
Z1: Zener TZM5224B-GS08; D_MiniMELF

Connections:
0: C1.1, CP1.2 (VCC-), J2.2, K1.2 (-_CONTROL), PS1.4 (0V), R3.2, R5.1, Z1.2
+5V: C1.2, CP1.5 (VCC+), PS1.6 (+VO), R2.2, R6.2
+5VA: J1.2, K1.4 (LOAD_2), PS1.1 (VIN), R8.2
+BATT: J2.1, R1.2
Comp: CP1.1 (OUT), K1.1 (+_CONTROL), R6.1
Exit: J1.1, R4.2, R8.1, R9.2
GND: J1.3, PS1.2 (GND), R7.1, R9.1
unnamed: CP1.4 (IN+), R2.1, R3.1
unnamed: CP1.3 (IN-), F1.2, R5.2, Z1.1
unnamed: F1.1, R1.1
Raw_Exit: K1.3 (LOAD_1), R4.1, R7.2

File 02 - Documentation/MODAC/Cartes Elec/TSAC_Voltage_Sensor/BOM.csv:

"Reference","Value","Qty","Manufacturer_Name","Manufacturer_Part_Number"
"C1","Condensateur 0805Y1000104JXT","1","Syfer","0805Y1000104JXT"
"CP1","Comparateur TS391ILT","1","STMicroelectronics","TS391ILT"
"F1","Fuse","1","",""
"J1","3P Droit 22-11-2032","1","",""
"J2","200241-1112","1","Molex","200241-1112"
"K1","SSR CPC1394GR","1","LITTELFUSE","CPC1394GR"
"PS1","Alim Iso PDM2-S5-S5-S","1","CUI Inc.","PDM2-S5-S5-S"
"R1","820k","1","KOA Speer","RK73H2BLTDD2152F"
"R2","1k2","1","KOA Speer","RK73H2BLTDD2152F"
"R3","1k","1","KOA Speer","RK73H2BLTDD2152F"
"R4","3k9","1","KOA Speer","RK73H2BLTDD2152F"
"R5","33k","1","KOA Speer","RK73H2BLTDD2152F"
"R6","2k7","1","KOA Speer","RK73H2BLTDD2152F"
"R7","2k","1","KOA Speer","RK73H2BLTDD2152F"
"R8,R9","8k2","2","KOA Speer","RK73H2BLTDD2152F"
"Z1","Zener TZM5224B-GS08","1","Vishay","TZM5224B-GS08"

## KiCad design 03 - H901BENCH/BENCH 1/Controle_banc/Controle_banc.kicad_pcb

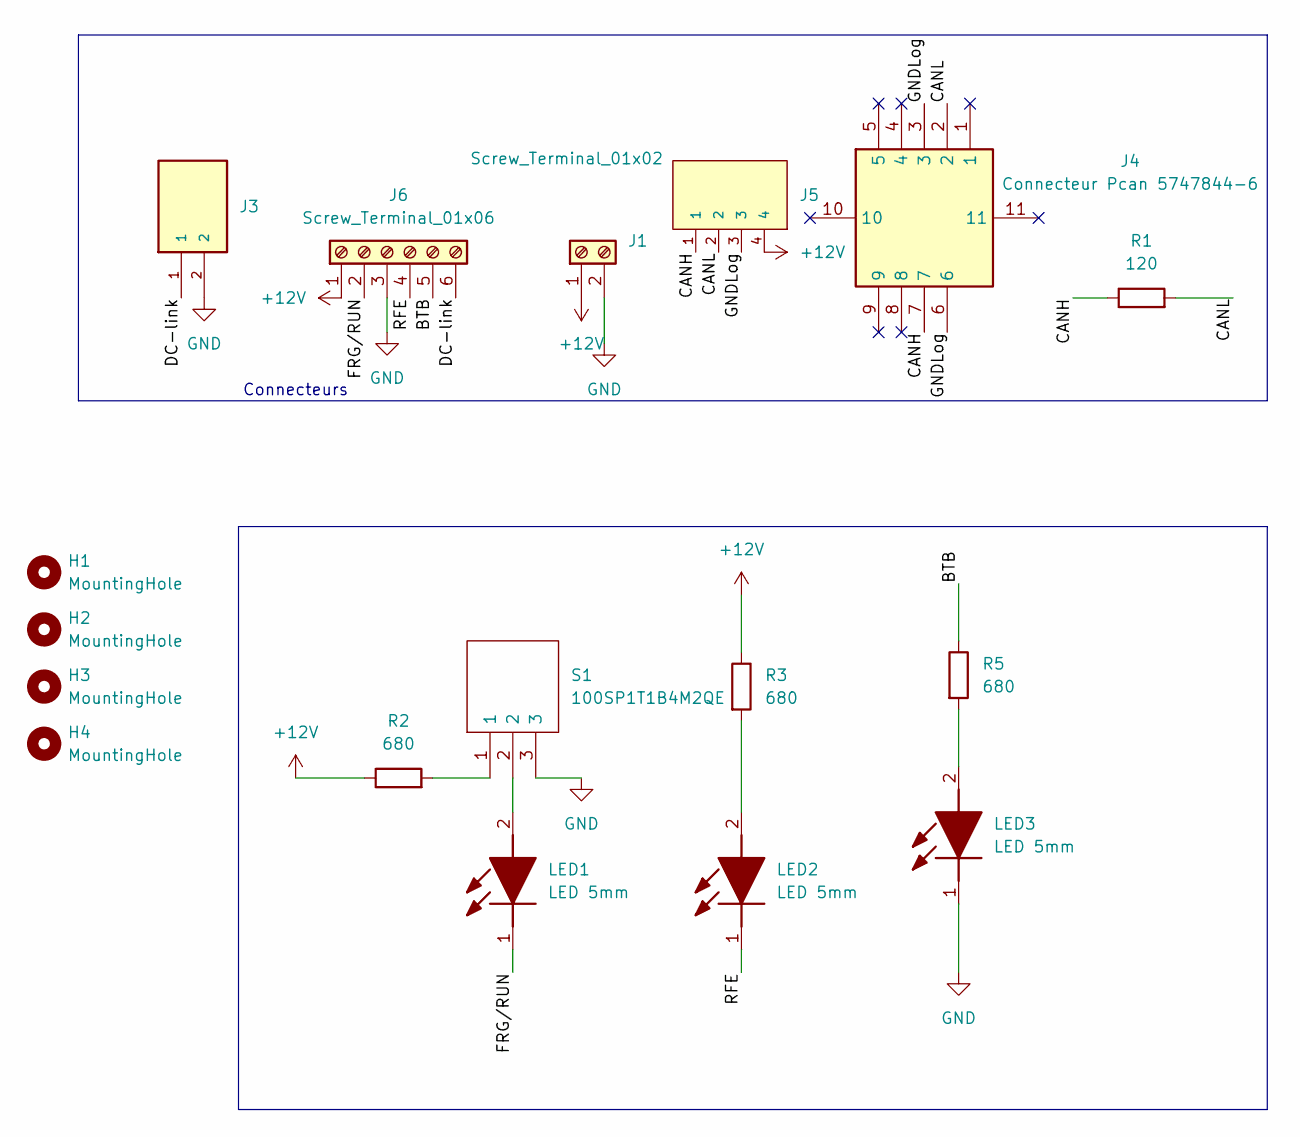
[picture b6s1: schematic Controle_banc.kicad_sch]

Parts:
H1, H2, H3, H4: MountingHole; MountingHole_4mm
J1: Screw_Terminal_01x02; TerminalBlock_bornier-2_P5.08mm
J3: 2P Droit 22-11-2022; MOLEX_22-11-2022; Manufacturer_Part_Number 22-11-2022; Mouser Part Number 538-22-11-2022
J4: Connecteur Pcan 5747844-6; 57478446; Mouser Part Number 571-5747844-6
J5: 4P Droit 22-11-2042; MOLEX_22-11-2042; Manufacturer_Part_Number 22-11-2042; Mouser Part Number 538-22-11-2042
J6: Screw_Terminal_01x06; TerminalBlock_bornier-6_P5.08mm
LED1, LED2, LED3: LED 5mm; 4302H55V; Mouser Part Number 606-4302H5-5V
R1: 120; R_Axial_DIN0207_L6.3mm_D2.5mm_P10.16mm_Horizontal
R2, R3, R5: 680; R_Axial_DIN0207_L6.3mm_D2.5mm_P10.16mm_Horizontal
S1: 100SP1T1B4M2QE; Mouser Part Number 612-100-A1421

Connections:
+12V: J1.1, J5.4, J6.1, R2.1, R3.1
/BTB: J6.5, R5.1
/CANH: J4.7, J5.1, R1.1
/CANL: J4.2, J5.2, R1.2
/DC-link: J3.1, J6.6
/FRG/RUN: J6.2, LED1.1 (K)
/GNDLog: J4.3, J4.6, J5.3
/RFE: J6.4, LED2.1 (K)
GND: J1.2, J3.2, J6.3, LED3.1 (K), S1.3
unnamed: LED1.2 (A), S1.2
unnamed: LED2.2 (A), R3.2
unnamed: LED3.2 (A), R5.2
unnamed: R2.2, S1.1

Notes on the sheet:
Connecteurs
